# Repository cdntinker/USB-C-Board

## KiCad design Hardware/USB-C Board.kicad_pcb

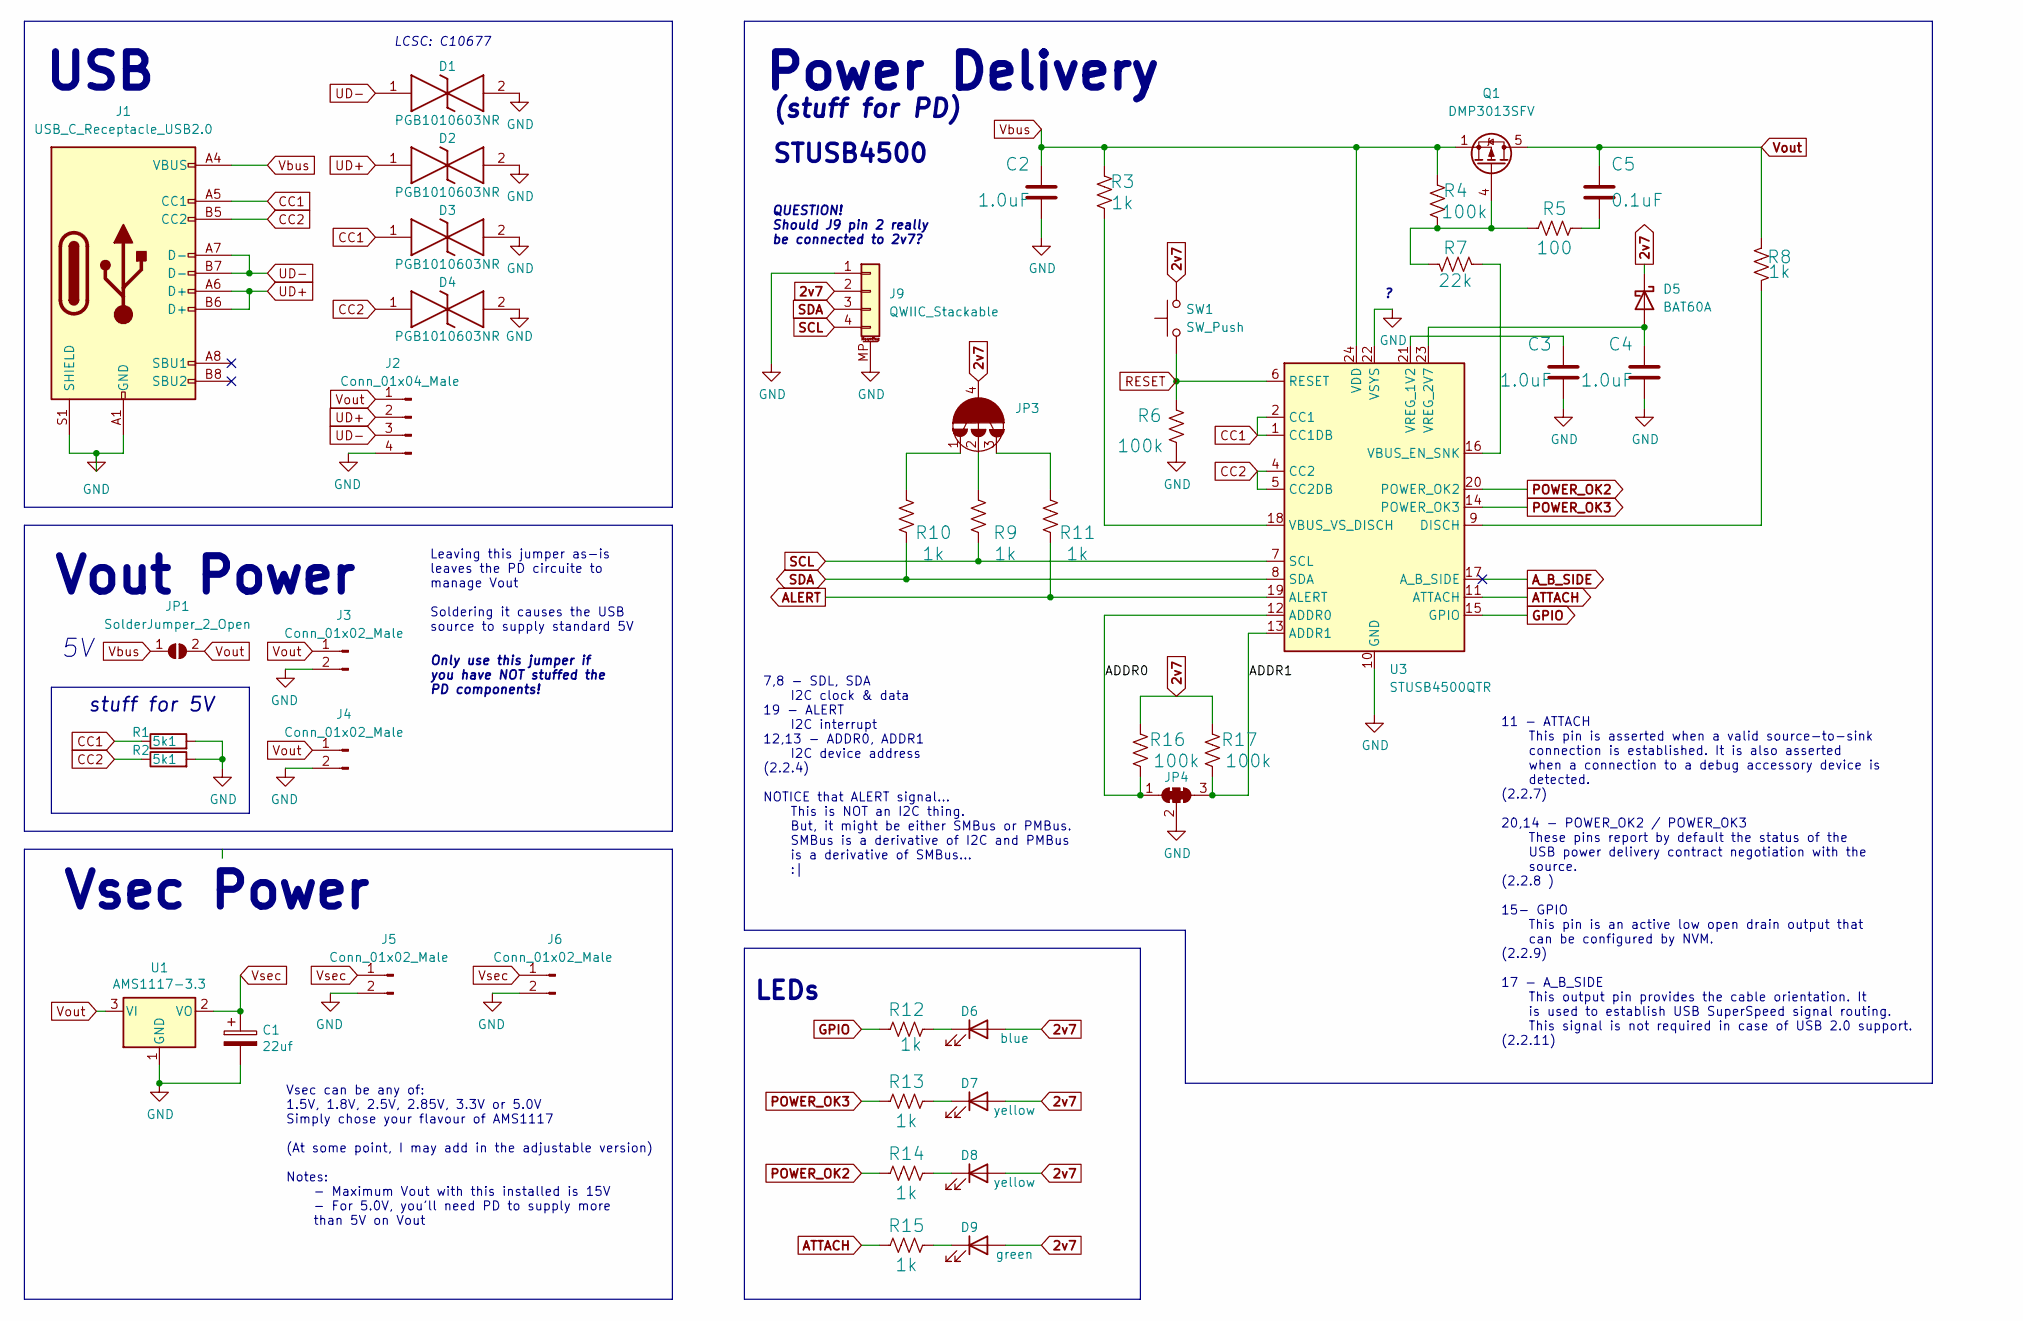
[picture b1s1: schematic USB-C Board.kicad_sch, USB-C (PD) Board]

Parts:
C1: 22uf; CP_EIA-6032-28-Tantalumm_HandSolder
C2, C3, C4: 1.0uF; C_0603_1608Metric
C5: 0.1uF; C_0603_1608Metric
D1, D2, D3, D4: PGB1010603NR; PGB1010603NRHF; Manufacturer_Part_Number PGB1010603NR; Mouser Part Number 576-PGB1010603NR
D5: BAT60A; D_SOD-323
D6: blue; LED_0603_1608Metric
D7, D8: yellow; LED_0603_1608Metric
D9: green; LED_0603_1608Metric
J1: USB_C_Receptacle_USB2.0; USB_C_Receptacle_HRO_TYPE-C-31-M-12
J2: Conn_01x04_Male; PinHeader_1x04_P2.54mm_Vertical
J3, J4, J5, J6: Conn_01x02_Male; PinHeader_1x02_P2.54mm_Vertical
J9: QWIIC_Stackable
JP1: SolderJumper_2_Open; SolderJumper-2_P1.3mm_Open_RoundedPad1.0x1.5mm
JP3: SolderJumper_4_Bridged; SolderJumper-2_P1.3mm_Open_RoundedPad1.0x1.5mm
JP4: SolderJumper_3_Bridged123; SolderJumper-3_P1.3mm_Bridged123_Pad1.0x1.5mm
Q1: DMP3013SFV; Diodes_PowerDI3333-8
R1, R2: 5k1; R_0603_1608Metric_Pad0.98x0.95mm_HandSolder
R3, R8, R9, R10, R11, R12, R13, R14, R15: 1k; R_0603_1608Metric
R4, R6, R16, R17: 100k; R_0603_1608Metric
R5: 100; R_0603_1608Metric
R7: 22k; R_0603_1608Metric
SW1: SW_Push; SW_Push_TS273014TP
U1: AMS1117-3.3; SOT-223-3_TabPin2
U3: STUSB4500QTR; QFN-24-1EP_4x4mm_P0.5mm_EP2.7x2.7mm

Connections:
2v7: D5.1 (K), D6.2 (A), D7.2 (A), D8.2 (A), D9.2 (A), J9.2, JP3.4 (B), R16.2, R17.2, SW1.2
/ADDR0: JP4.1 (A), R16.1, U3.12 (ADDR0)
/ADDR1: JP4.3 (B), R17.1, U3.13 (ADDR1)
ALERT: R11.1, U3.19 (ALERT)
ATTACH: R15.1, U3.11 (ATTACH)
A_B_SIDE: U3.17 (A_B_SIDE)
CC1: D3.1, J1.A5 (CC1), R1.1, U3.1 (CC1DB), U3.2 (CC1)
CC2: D4.1, J1.B5 (CC2), R2.1, U3.4 (CC2), U3.5 (CC2DB)
GND: C1.2, C2.2, C3.2, C4.2, D1.2, D2.2, D3.2, D4.2, J1.A1 (GND), J1.A12 (GND), J1.B1 (GND), J1.B12 (GND), J1.S1 (SHIELD), J2.4, J3.2, J4.2, J5.2, J6.2, J9.1, J9.MP (MountPin), JP4.2 (C), R1.2, R2.2, R6.1, U1.1 (GND), U3.10 (GND), U3.22 (VSYS), U3.25 (GND)
GPIO: R12.1, U3.15 (GPIO)
unnamed: C5.2, R5.2
unnamed: C4.1, D5.2 (A), U3.23 (VREG_2V7)
unnamed: D7.1 (K), R13.2
unnamed: D9.1 (K), R15.2
unnamed: JP3.2 (B), R9.2
unnamed: JP3.3 (B), R11.2
unnamed: Q1.4 (G), R4.1, R5.1, R7.1
unnamed: JP3.1 (A), R10.2
unnamed: D6.1 (K), R12.2
unnamed: D8.1 (K), R14.2
unnamed: R8.2, U3.9 (DISCH)
unnamed: R7.2, U3.16 (VBUS_EN_SNK)
unnamed: R3.1, U3.18 (VBUS_VS_DISCH)
unnamed: C3.1, U3.21 (VREG_1V2)
POWER_OK2: R14.1, U3.20 (POWER_OK2)
POWER_OK3: R13.1, U3.14 (POWER_OK3)
RESET: R6.2, SW1.1, U3.6 (RESET)
SCL: J9.4, R9.1, U3.7 (SCL)
SDA: J9.3, R10.1, U3.8 (SDA)
UD+: D2.1, J1.A6 (D+), J1.B6 (D+), J2.2
UD-: D1.1, J1.A7 (D-), J1.B7 (D-), J2.3
Vbus: C2.1, J1.A4 (VBUS), J1.A9 (VBUS), J1.B4 (VBUS), J1.B9 (VBUS), JP1.1 (A), Q1.1 (S), Q1.2 (S), Q1.3 (S), R3.2, R4.2, U3.24 (VDD)
Vout: C5.1, J2.1, J3.1, J4.1, JP1.2 (B), Q1.5 (D), R8.1, U1.3 (VI)
Vsec: C1.1, J5.1, J6.1, U1.2 (VO)

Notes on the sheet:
Vsec Power
Vout Power
Only use this jumper if you have NOT stuffed the PD components!
QUESTION! Should J9 pin 2 really be connected to 2v7?
stuff for 5V
STUSB4500
LCSC: C10677
USB
7,8 - SDL, SDA I2C clock & data 19 - ALERT I2C interrupt 12,13 - ADDR0, ADDR1 I2C device address (2.2.4) NOTICE that ALERT signal... This is NOT an I2C thing. But, it might be either SMBus or PMBus. SMBus is a derivative of I2C and PMBus is a derivative of SMBus... :|
(stuff for PD)
Power Delivery
Vsec can be any of: 1.5V, 1.8V, 2.5V, 2.85V, 3.3V or 5.0V Simply chose your flavour of AMS1117 (At some point, I may add in the adjustable version) Notes: - Maximum Vout with this installed is 15V - For 5.0V, you'll need PD to supply more than 5V on Vout
Leaving this jumper as-is leaves the PD circuite to manage Vout Soldering it causes the USB source to supply standard 5V
11 - ATTACH This pin is asserted when a valid source-to-sink connection is established. It is also asserted when a connection to a debug accessory device is detected. (2.2.7) 20,14 - POWER_OK2 / POWER_OK3 These pins report by default the status of the USB power delivery contract negotiation with th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
LEDs

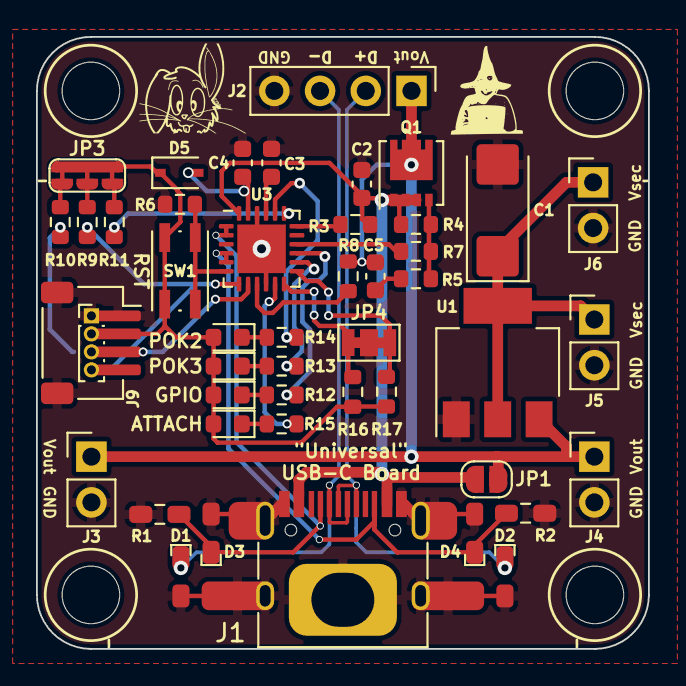
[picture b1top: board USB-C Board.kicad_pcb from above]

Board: 2 copper layers, 34.0 x 34.0 mm, 45 parts (0 on the bottom side), 33 nets.

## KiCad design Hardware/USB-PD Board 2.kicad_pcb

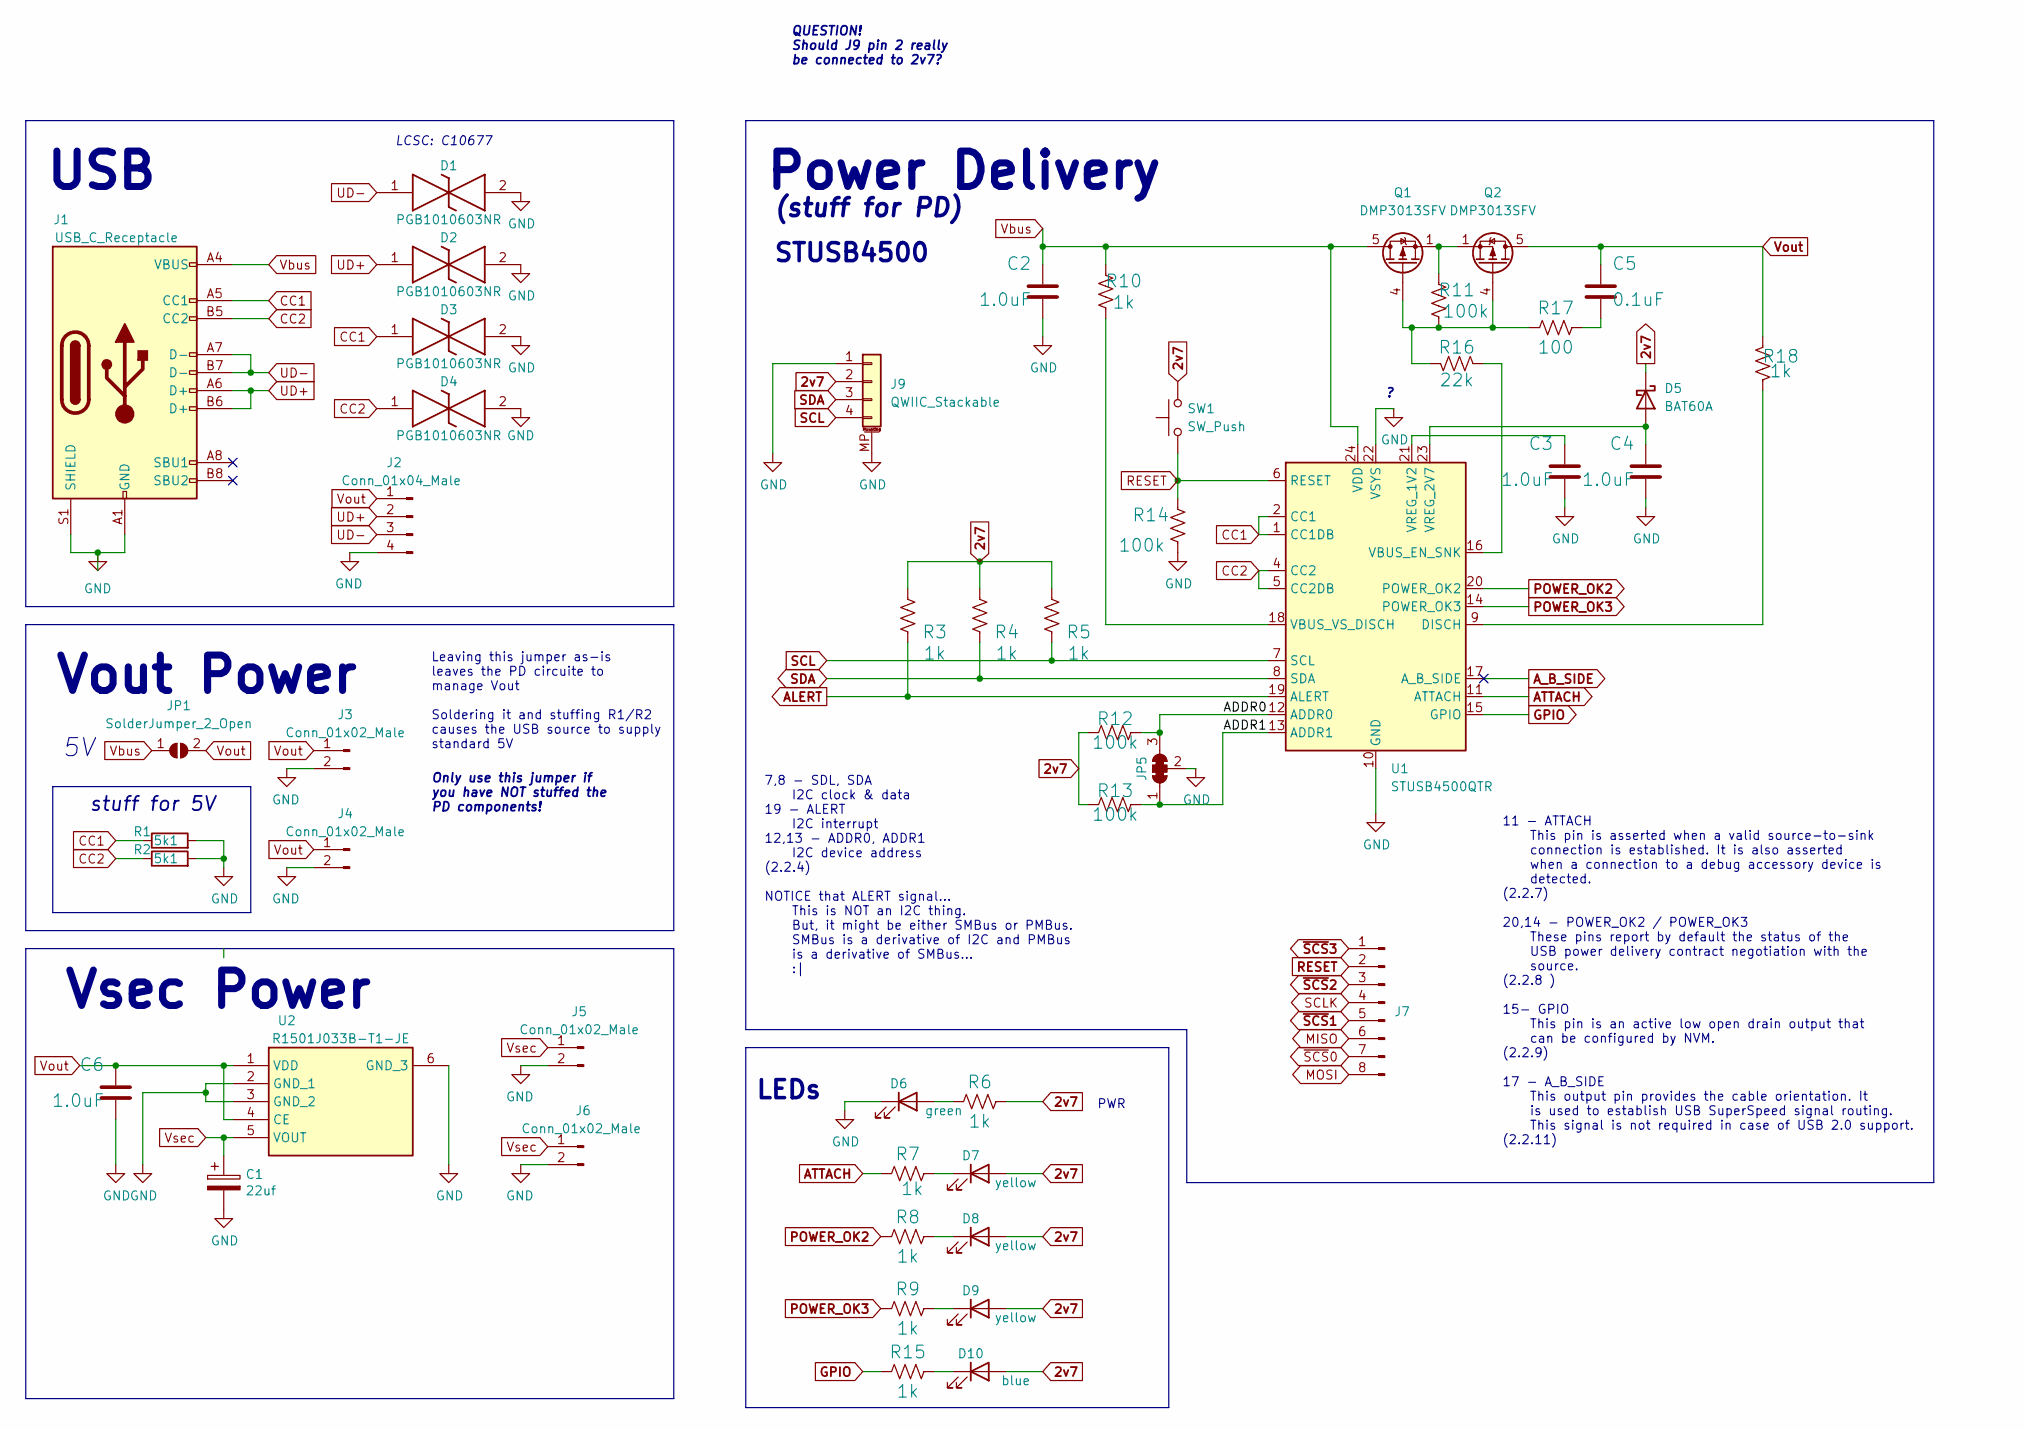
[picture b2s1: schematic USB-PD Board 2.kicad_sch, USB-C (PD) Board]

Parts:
C1: 22uf; CP_EIA-6032-28-Tantalumm_HandSolder; LCSC C145122
C2, C3, C4, C6: 1.0uF; C_0603_1608Metric; LCSC C559769
C5: 0.1uF; C_0603_1608Metric; LCSC C14663
D1, D2, D3, D4: PGB1010603NR; PGB1010603NRHF; Manufacturer_Part_Number PGB1010603NR; Mouser Part Number 576-PGB1010603NR
D5: BAT60A; D_SOD-323; LCSC C5355496
D6: green; LED_0603_1608Metric; LCSC C434420
D7: yellow; LED_0603_1608Metric; LCSC C434421
D8, D9: yellow; LED_0603_1608Metric; LCSC C434424
D10: blue; LED_0603_1608Metric; LCSC C434420
J1: USB_C_Receptacle; USB_C_Receptacle_HRO_TYPE-C-31-M-12; LCSC C2765186
J2: Conn_01x04_Male; Board_Stacker_4
J3, J4, J5, J6: Conn_01x02_Male; Board_Stacker_2
J7: Conn_01x08_Male; PinHeader_2x04_P1.27mm_Vertical; LCSC C2881786 + C2684732
J9: QWIIC_Stackable; QWIIC_Stack_II
JP1: SolderJumper_2_Open; SolderJumper-2_P_Open_Rounded_skinny
JP5: SolderJumper_3_Bridged123; SolderJumper-3_P1.3mm_Bridged123_Pad1.0x1.5mm
Q1, Q2: DMP3013SFV; Diodes_PowerDI3333-8; LCSC C264098
R1, R2: 5k1; R_0603_1608Metric_Pad0.98x0.95mm_HandSolder; LCSC C23186
R3, R4, R5, R6, R7, R8, R9, R10, R15, R18: 1k; R_0603_1608Metric; LCSC C21190
R11, R12, R13, R14: 100k; R_0603_1608Metric; LCSC C25803
R16: 22k; R_0603_1608Metric; LCSC C31850
R17: 100; R_0603_1608Metric; LCSC C22775
SW1: SW_Push; SW_Push_TS273014TP; LCSC C2858276
U1: STUSB4500QTR; QFN-24-1EP_4x4mm_P0.5mm_EP2.7x2.7mm; LCSC C2678061
U2: R1501J033B-T1-JE; R1501J033BT1JE; Manufacturer_Part_Number R1501J033B-T1-JE; LCSC C3748149

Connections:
2v7: D5.1 (K), D7.2 (A), D8.2 (A), D9.2 (A), D10.2 (A), J9.2, R3.2, R4.2, R5.2, R6.2, R12.2, R13.2, SW1.2
/ADDR0: JP5.3 (B), R12.1, U1.12 (ADDR0)
/ADDR1: JP5.1 (A), R13.1, U1.13 (ADDR1)
ALERT: R3.1, U1.19 (ALERT)
ATTACH: R7.1, U1.11 (ATTACH)
A_B_SIDE: U1.17 (A_B_SIDE)
CC1: D3.1, J1.A5 (CC1), R1.1, U1.1 (CC1DB), U1.2 (CC1)
CC2: D4.1, J1.B5 (CC2), R2.1, U1.4 (CC2), U1.5 (CC2DB)
GND: C1.2, C2.2, C3.2, C4.2, C6.2, D1.2, D2.2, D3.2, D4.2, D6.1 (K), J1.A1 (GND), J1.A12 (GND), J1.B1 (GND), J1.B12 (GND), J1.S1 (SHIELD), J2.4, J3.2, J4.2, J5.2, J6.2, J9.1, J9.MP (MountPin), JP5.2 (C), R1.2, R2.2, R14.1, U1.10 (GND), U1.22 (VSYS), U1.25 (GND), U2.2 (GND_1), U2.3 (GND_2), U2.6 (GND_3)
GPIO: R15.1, U1.15 (GPIO)
MISO: J7.6
MOSI: J7.8
unnamed: C3.1, U1.21 (VREG_1V2)
unnamed: C4.1, D5.2 (A), U1.23 (VREG_2V7)
unnamed: C5.2, R17.2
unnamed: D6.2 (A), R6.1
unnamed: D7.1 (K), R7.2
unnamed: D8.1 (K), R8.2
unnamed: D9.1 (K), R9.2
unnamed: D10.1 (K), R15.2
unnamed: Q1.1 (S), Q1.2 (S), Q1.3 (S), Q2.1 (S), Q2.2 (S), Q2.3 (S), R11.2
unnamed: Q1.4 (G), Q2.4 (G), R11.1, R16.1, R17.1
unnamed: R10.1, U1.18 (VBUS_VS_DISCH)
unnamed: R16.2, U1.16 (VBUS_EN_SNK)
unnamed: R18.2, U1.9 (DISCH)
POWER_OK2: R8.1, U1.20 (POWER_OK2)
POWER_OK3: R9.1, U1.14 (POWER_OK3)
RESET: J7.2, R14.2, SW1.1, U1.6 (RESET)
SCL: J9.4, R5.1, U1.7 (SCL)
SCLK: J7.4
SDA: J9.3, R4.1, U1.8 (SDA)
UD+: D2.1, J1.A6 (D+), J1.B6 (D+), J2.2
UD-: D1.1, J1.A7 (D-), J1.B7 (D-), J2.3
Vbus: C2.1, J1.A4 (VBUS), J1.A9 (VBUS), J1.B4 (VBUS), J1.B9 (VBUS), JP1.1 (A), Q1.5 (D), R10.2, U1.24 (VDD)
Vout: C5.1, C6.1, J2.1, J3.1, J4.1, JP1.2 (B), Q2.5 (D), R18.1, U2.1 (VDD), U2.4 (CE)
Vsec: C1.1, J5.1, J6.1, U2.5 (VOUT)
~SCS0: J7.7
~SCS1: J7.5
~SCS2: J7.3
~SCS3: J7.1

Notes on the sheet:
Vsec Power
Vout Power
Only use this jumper if you have NOT stuffed the PD components!
QUESTION! Should J9 pin 2 really be connected to 2v7?
stuff for 5V
STUSB4500
LCSC: C10677
USB
7,8 - SDL, SDA I2C clock & data 19 - ALERT I2C interrupt 12,13 - ADDR0, ADDR1 I2C device address (2.2.4) NOTICE that ALERT signal... This is NOT an I2C thing. But, it might be either SMBus or PMBus. SMBus is a derivative of I2C and PMBus is a derivative of SMBus... :|
(stuff for PD)
Power Delivery
Leaving this jumper as-is leaves the PD circuite to manage Vout Soldering it and stuffing R1/R2 causes the USB source to supply standard 5V
PWR
11 - ATTACH This pin is asserted when a valid source-to-sink connection is established. It is also asserted when a connection to a debug accessory device is detected. (2.2.7) 20,14 - POWER_OK2 / POWER_OK3 These pins report by default the status of the USB power delivery contract negotiation with th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
LEDs

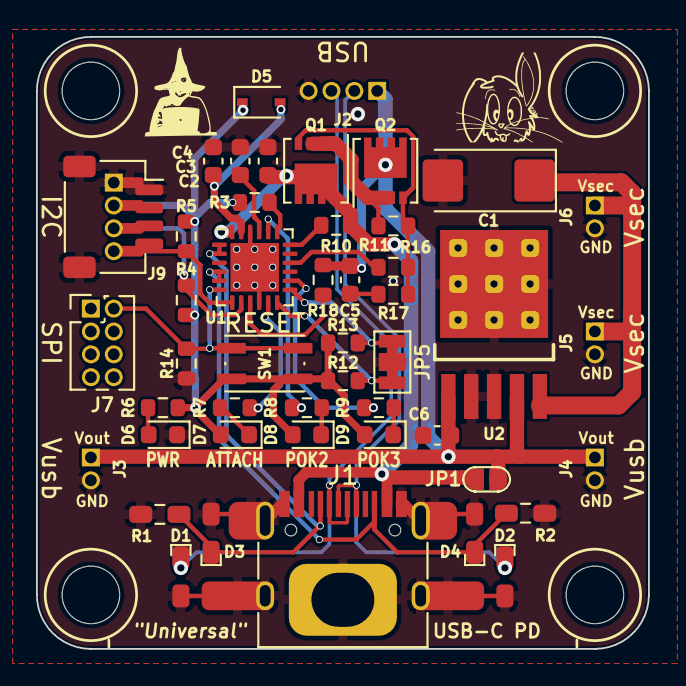
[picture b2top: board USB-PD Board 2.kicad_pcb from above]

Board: 2 copper layers, 34.0 x 34.0 mm, 47 parts (0 on the bottom side), 30 nets.

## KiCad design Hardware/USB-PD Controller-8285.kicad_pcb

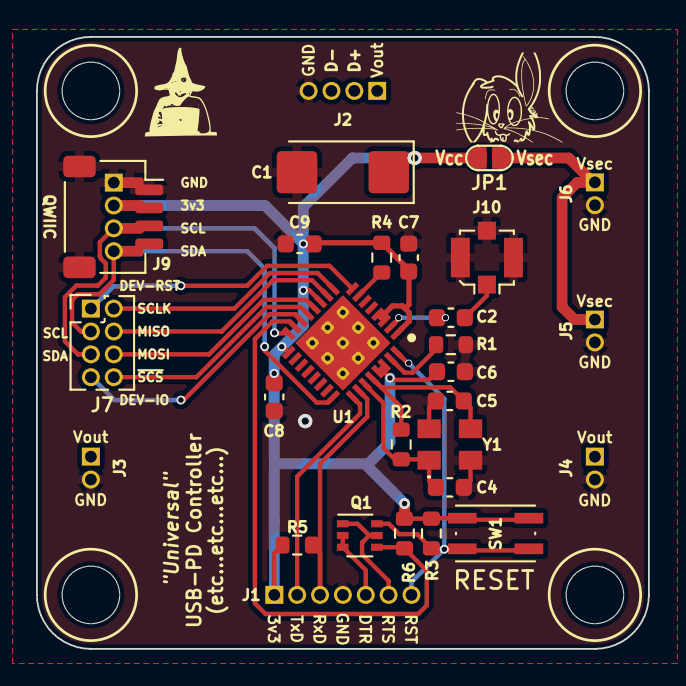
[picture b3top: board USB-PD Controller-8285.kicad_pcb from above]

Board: 2 copper layers, 34.0 x 34.0 mm, 28 parts (0 on the bottom side), 23 nets.

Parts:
C1: 22uf; CP_EIA-6032-28-Tantalumm_HandSolder
C2: 5.6pf; C_0603_1608Metric
C4, C5: 20pf; C_0603_1608Metric
C6, C7, C8, C9: 1uf; C_0603_1608Metric
J1: Conn_01x07_Male; Board_Stacker_7
J2: Conn_01x04_Male; Board_Stacker_4
J3, J4, J5, J6: Conn_01x02_Male; Board_Stacker_2
J7: Conn_01x08_Male; PinHeader_2x04_P1.27mm_Vertical
J9: QWIIC_Stackable; QWIIC_Stack_II
J10: Conn_Coaxial; U.FL_Molex_MCRF_73412-0110_Vertical
JP1: SolderJumper_2_Open; SolderJumper-2_P_Open_Rounded_skinny
Q1: UMH3N; SOT-363_SC-70-6
R1: 12K; R_0603_1608Metric
R2: 1M; R_0603_1608Metric
R3, R4, R5, R6: 10K; R_0603_1608Metric
SW1: SW_Push; SW_Push_TS273014TP
U1: ESP8285H16; QFN50P500X500X90-33N-D
Y1: 26.000MHz; ABM825000MHz10B1UT

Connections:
+3V3: C1.1, C6.2, C7.2, C8.2, C9.2, J1.1, J9.2, JP1.2 (B), R3.2, R4.2, R5.2, R6.2, SW1.2, U1.1 (VDDA_1), U1.3 (VDD3P3_1), U1.4 (VDD3P3_2), U1.11 (VDDPST_1), U1.17 (VDDPST_2), U1.29 (VDDD), U1.30 (VDDA_2)
/CHIP_EN: R4.1, U1.7 (CHIP_EN)
/DTR: J1.5, Q1.2 (B1), Q1.3 (C2)
/LNA: C2.1, U1.2 (LNA)
/RES12K: R1.2, U1.31 (RES12K)
/RTS: J1.6, Q1.1 (E1), Q1.5 (B2)
/eXi: C5.2, R2.2, U1.28 (XTAL_IN), Y1.3 (Xt_2)
/eXo: C4.2, R2.1, U1.27 (XTAL_OUT), Y1.1 (Xt_1)
ALERT: J7.7, U1.14 (GPIO2)
ATTACH: J7.2, U1.9 (MTMS)
GND: C1.2, C4.1, C5.1, C6.1, C7.1, C8.1, C9.1, J1.4, J2.4, J3.2, J4.2, J5.2, J6.2, J9.1, J9.MP (MountPin), J10.2 (Ext), R1.1, U1.33 (EP), Y1.2 (G_1), Y1.4 (G_2)
IO0: Q1.4 (E2), R6.1, U1.15 (GPIO0)
IO1: J1.3, R5.1, U1.26 (U0TXD)
IO3: J1.2, U1.25 (U0RXD)
IO12: J7.4, U1.10 (MTDI)
IO13: J7.6, U1.12 (MTCK)
IO15: J7.8, U1.13 (MTDO)
IO16: J7.1, U1.8 (XDP_DCDC)
unnamed: C2.2, J10.1 (In)
RST: J1.7, Q1.6 (C1), R3.1, SW1.1, U1.32 (EXT_RSTB)
SCL: J7.3, J9.4, U1.24 (GPIO5)
SDA: J7.5, J9.3, U1.16 (GPIO4)
Vsec: J5.1, J6.1, JP1.1 (A)

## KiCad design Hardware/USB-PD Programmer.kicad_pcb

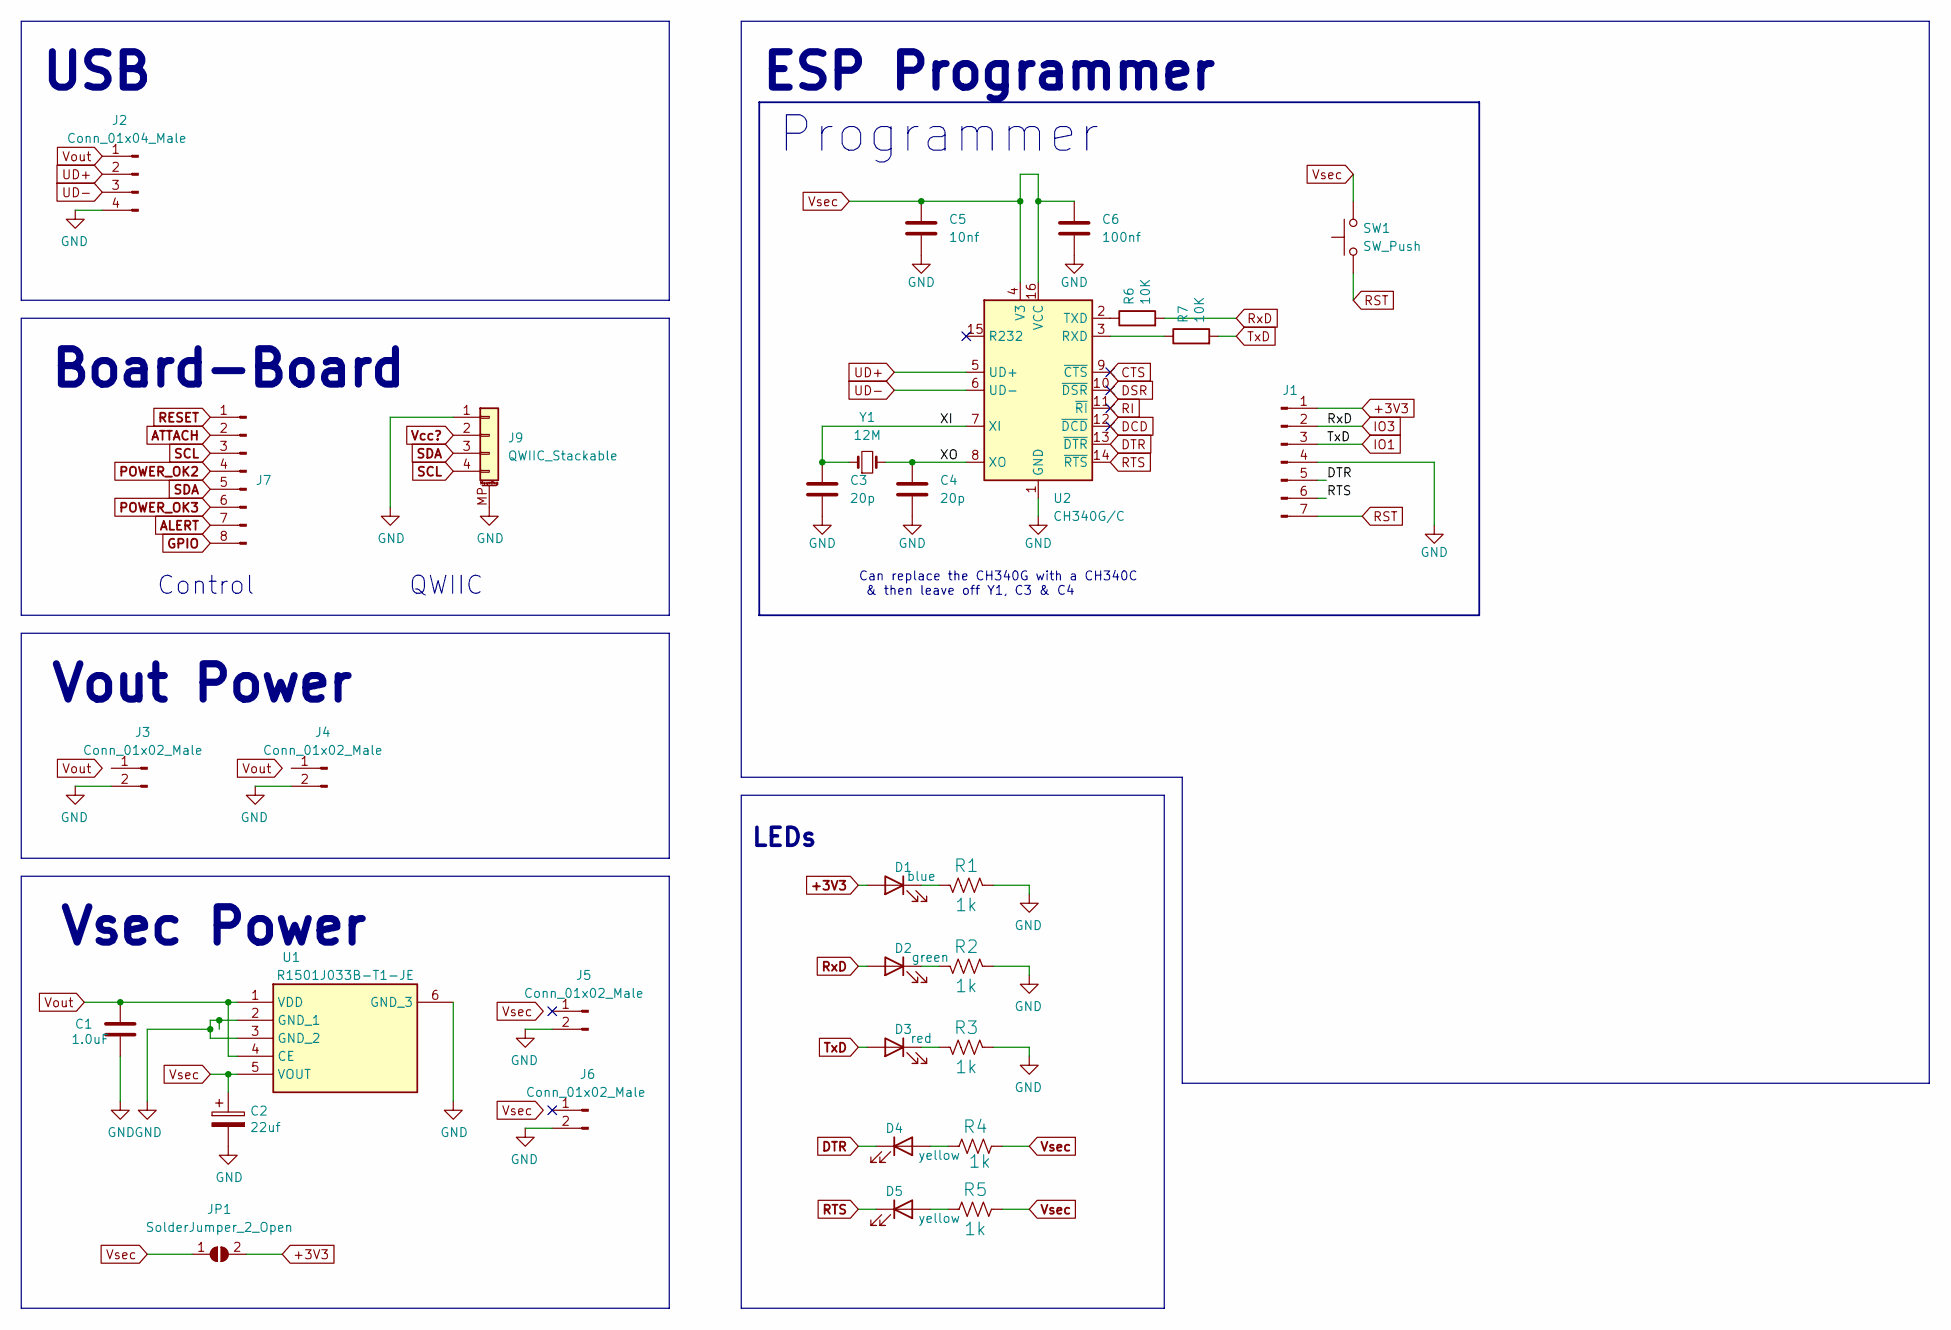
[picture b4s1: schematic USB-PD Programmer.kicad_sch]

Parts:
C1: 1.0uF; C_0603_1608Metric; LCSC C559769
C2: 22uf; CP_EIA-6032-28-Tantalumm_HandSolder; LCSC C89246
C3, C4: 20p; C_0603_1608Metric_Pad1.08x0.95mm_HandSolder; LCSC C325469
C5: 10nf; C_0603_1608Metric_Pad1.08x0.95mm_HandSolder; LCSC C161232
C6: 100nf; C_0603_1608Metric_Pad1.08x0.95mm_HandSolder; LCSC C235731
D1: blue; LED_0603_1608Metric; LCSC C434420
D2: green; LED_0603_1608Metric; LCSC C434420
D3: red; LED_0603_1608Metric; LCSC C434420
D4: yellow; LED_0603_1608Metric; LCSC C434421
D5: yellow; LED_0603_1608Metric; LCSC C434424
J1: Conn_01x07_Male; Board_Stacker_7
J2: Conn_01x04_Male; Board_Stacker_4
J3, J4, J5, J6: Conn_01x02_Male; Board_Stacker_2
J7: Conn_01x08_Male; PinHeader_2x04_P1.27mm_Vertical; LCSC C2881786 + C2684732
J9: QWIIC_Stackable
JP1: SolderJumper_2_Open; SolderJumper-2_P_Open_Rounded_skinny
R1, R2, R3, R4, R5: 1k; R_0603_1608Metric; LCSC C21190
R6, R7: 10K; R_0603_1608Metric_Pad0.98x0.95mm_HandSolder; LCSC C25804
SW1: SW_Push; SW_Push_TS273014TP; LCSC C2858276
U1: R1501J033B-T1-JE; R1501J033BT1JE; Manufacturer_Part_Number R1501J033B-T1-JE; LCSC C3748149
U2: CH340G/C; SOIC-16_3.9x9.9mm_P1.27mm; LCSC C14267/C84681
Y1: 12M; Crystal_SMD_5032-2Pin_5.0x3.2mm; LCSC C2842275

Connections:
+3V3: D1.2 (A), J1.1, JP1.2 (B)
/XI: C3.1, U2.7 (XI), Y1.1
/XO: C4.1, U2.8 (XO), Y1.2
ALERT: J7.7
ATTACH: J7.2
CTS: U2.9 (~CTS)
DCD: U2.12 (~DCD)
DSR: U2.10 (~DSR)
DTR: D4.1 (K), J1.5, U2.13 (~DTR)
GND: C1.2, C2.2, C3.2, C4.2, C5.2, C6.2, J1.4, J2.4, J3.2, J4.2, J5.2, J6.2, J9.1, J9.MP (MountPin), R1.1, R2.1, R3.1, U1.2 (GND_1), U1.3 (GND_2), U1.6 (GND_3), U2.1 (GND)
GPIO: J7.8
IO1: D3.2 (A), J1.3, R7.2
IO3: D2.2 (A), J1.2, R6.2
unnamed: D1.1 (K), R1.2
unnamed: D2.1 (K), R2.2
unnamed: D3.1 (K), R3.2
unnamed: D4.2 (A), R4.1
unnamed: D5.2 (A), R5.1
unnamed: R6.1, U2.2 (TXD)
unnamed: R7.1, U2.3 (RXD)
POWER_OK2: J7.4
POWER_OK3: J7.6
RESET: J7.1
RI: U2.11 (~RI)
RST: J1.7, SW1.1
RTS: D5.1 (K), J1.6, U2.14 (~RTS)
SCL: J7.3, J9.4
SDA: J7.5, J9.3
UD+: J2.2, U2.5 (UD+)
UD-: J2.3, U2.6 (UD-)
Vout: C1.1, J2.1, U1.1 (VDD), U1.4 (CE)
Vsec: C2.1, C5.1, C6.1, JP1.1 (A), R4.2, R5.2, SW1.2, U1.5 (VOUT), U2.4 (V3), U2.16 (VCC)

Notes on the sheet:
Vout Power
USB
Programmer
LEDs
Can replace the CH340G with a CH340C & then leave off Y1, C3 & C4
QWIIC
Board-Board
ESP Programmer
Vsec Power
Control

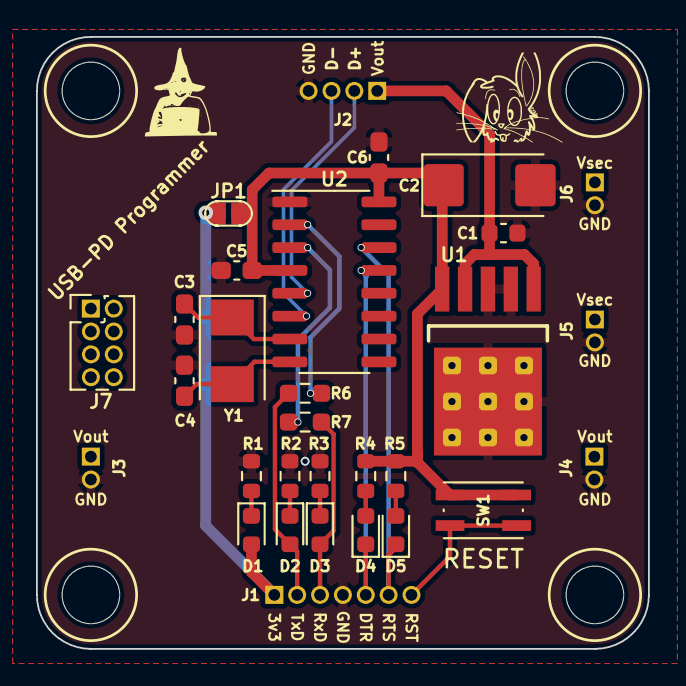
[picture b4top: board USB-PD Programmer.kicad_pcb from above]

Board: 2 copper layers, 34.0 x 34.0 mm, 30 parts (0 on the bottom side), 20 nets.

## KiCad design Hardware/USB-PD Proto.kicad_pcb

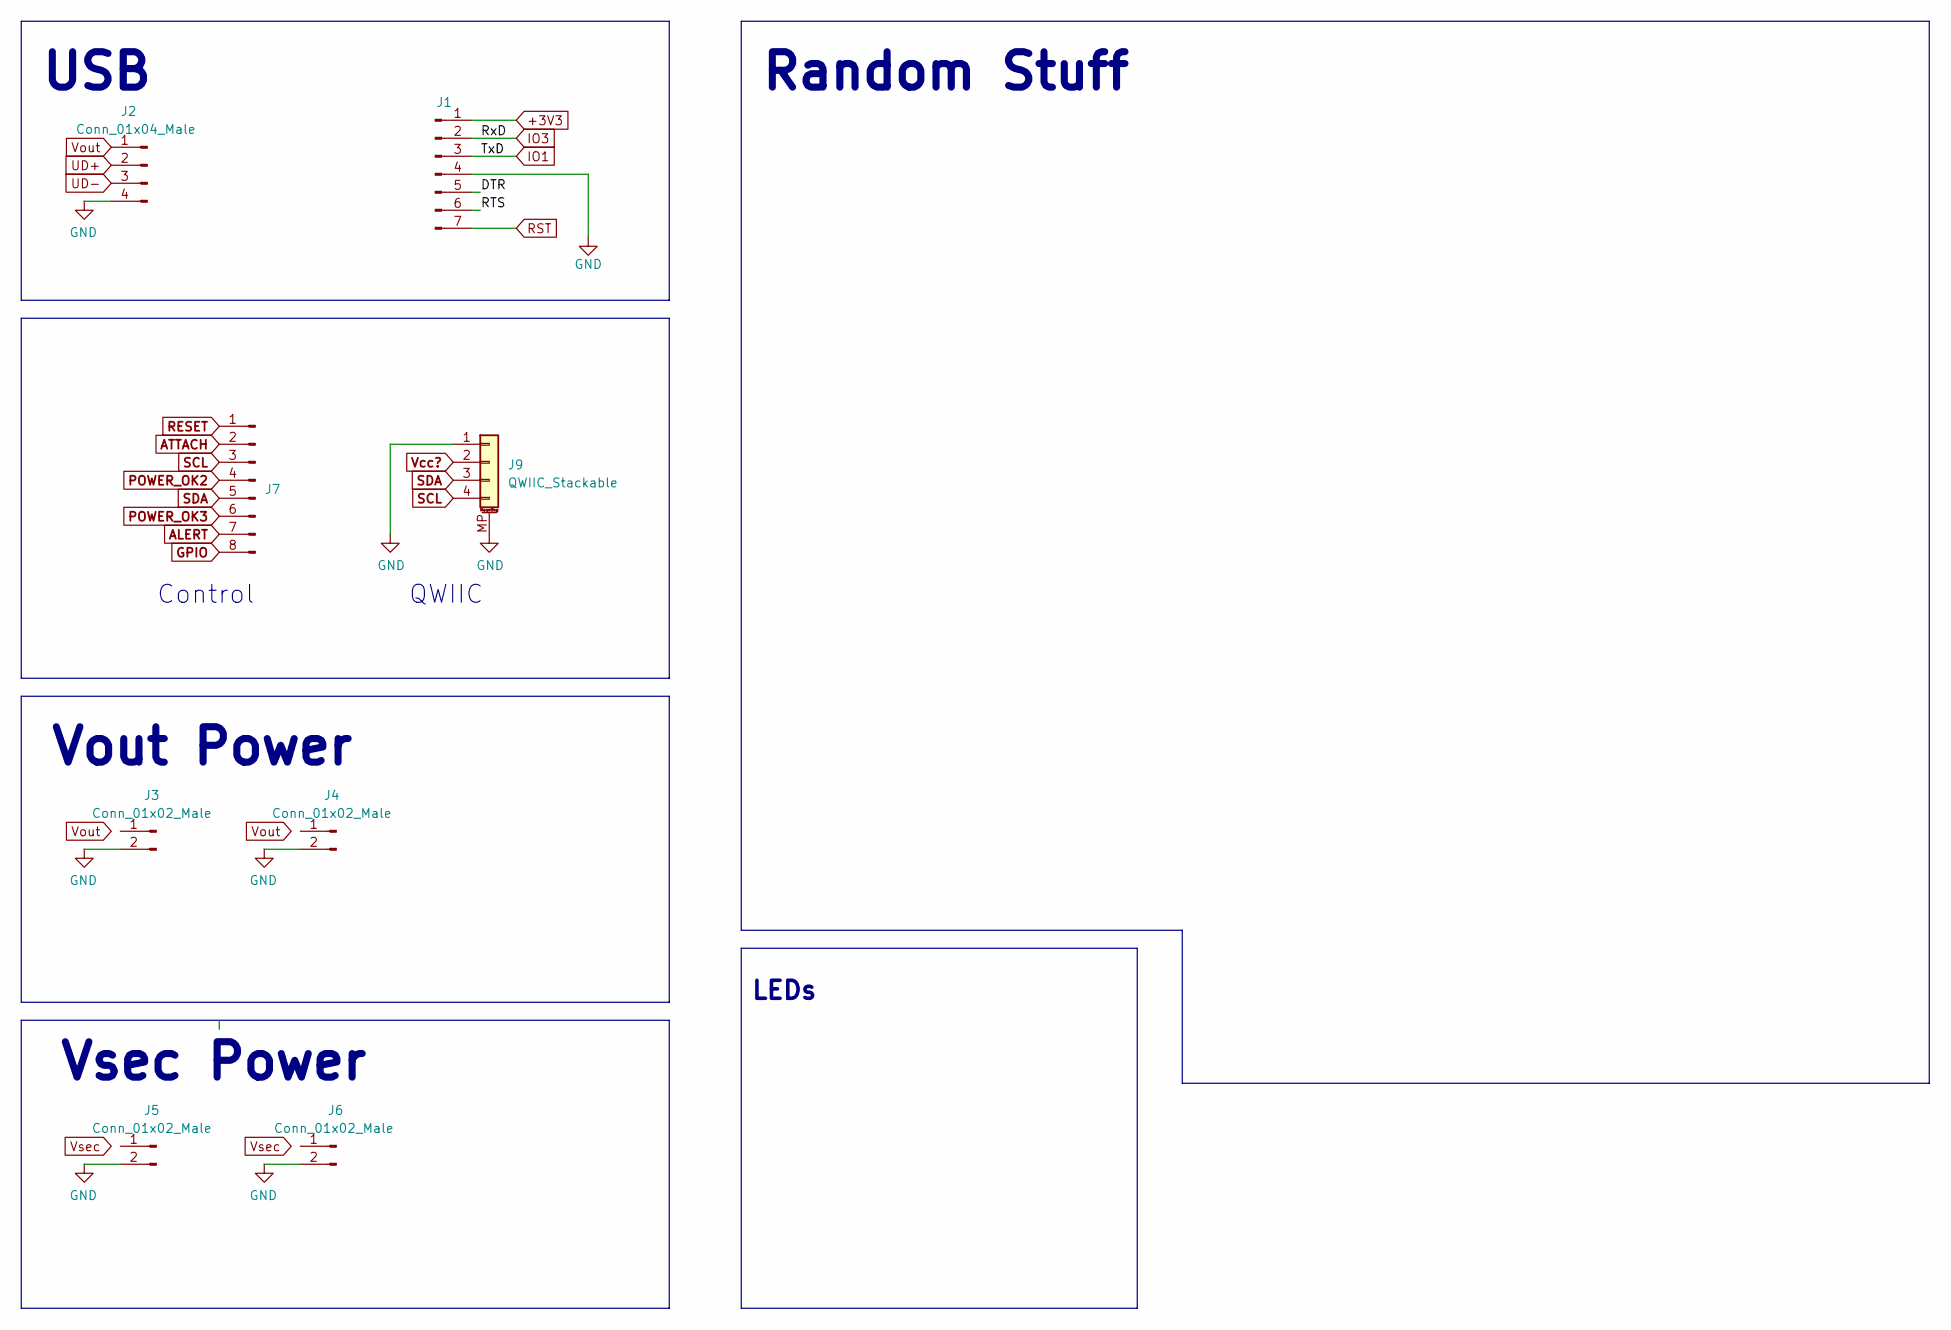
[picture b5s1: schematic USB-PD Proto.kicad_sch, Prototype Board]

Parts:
J1: Conn_01x07_Male; Board_Stacker_7
J2: Conn_01x04_Male; Board_Stacker_4
J3, J4, J5, J6: Conn_01x02_Male; Board_Stacker_2
J7: Conn_01x08_Male; PinHeader_2x04_P1.27mm_Vertical; LCSC C2881786 + C2684732
J9: QWIIC_Stackable; QWIIC_Stack_II

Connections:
+3V3: J1.1
/DTR: J1.5
/RTS: J1.6
ALERT: J7.7
ATTACH: J7.2
GND: J1.4, J2.4, J3.2, J4.2, J5.2, J6.2, J9.1, J9.MP (MountPin)
GPIO: J7.8
IO1: J1.3
IO3: J1.2
POWER_OK2: J7.4
POWER_OK3: J7.6
RESET: J7.1
RST: J1.7
SCL: J7.3, J9.4
SDA: J7.5, J9.3
UD+: J2.2
UD-: J2.3
Vcc?: J9.2
Vout: J2.1

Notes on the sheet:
Vsec Power
Vout Power
QWIIC
USB
Random Stuff
Control
LEDs

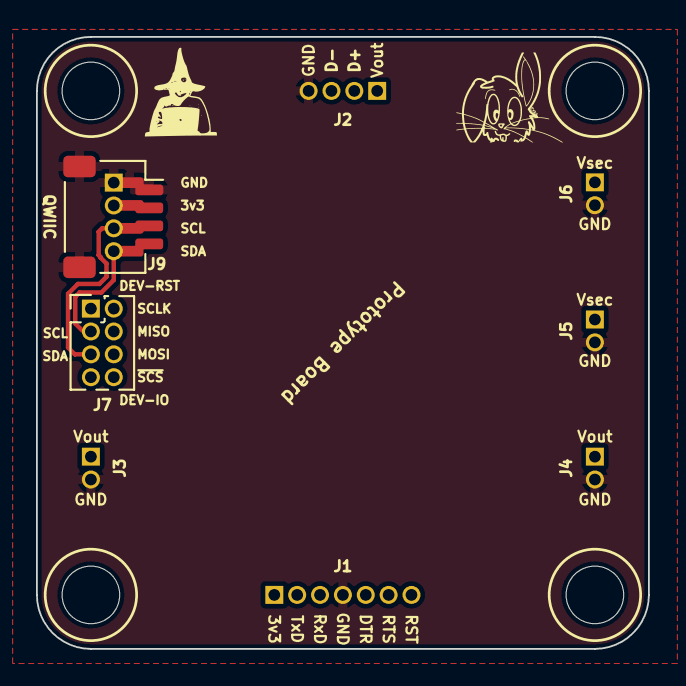
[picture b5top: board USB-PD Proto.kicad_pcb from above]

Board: 2 copper layers, 34.0 x 34.0 mm, 8 parts (0 on the bottom side), 3 nets.
